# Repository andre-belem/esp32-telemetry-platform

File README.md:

# Real-Time ESP32 Web Monitoring

Real-time IoT telemetry and remote monitoring platform using ESP32, MQTT, Node.js, Docker, and MySQL.

## Overview

This project was developed to demonstrate a complete IoT monitoring architecture capable of collecting, transmitting, storing, and visualizing real-time sensor data from an ESP32 device to a dedicated web server.

The system is designed with scalability and modularity in mind, combining embedded systems, backend development, networking, and data visualization technologies.

## Features

- Real-time sensor monitoring
- ESP32 Wi-Fi communication
- MQTT-based telemetry
- REST API integration
- Data storage using MySQL
- Web dashboard for live visualization
- Remote access through a dedicated Linux server
- Dockerized backend services
- Scalable IoT architecture

## System Architecture

````
+------------------+
|      ESP32       |
| Sensors & Data   |
+--------+---------+
         |
         | Wi-Fi / MQTT
         |
+--------v---------+
|   MQTT Broker    |
+--------+---------+
         |
         |
+--------v---------+
|  Node.js Backend |
|   REST API       |
+--------+---------+
         |
         |
+--------v---------+
|      MySQL       |
|   Data Storage   |
+--------+---------+
         |
         |
+--------v---------+
| Web Dashboard    |
| Real-Time Charts |
+------------------+

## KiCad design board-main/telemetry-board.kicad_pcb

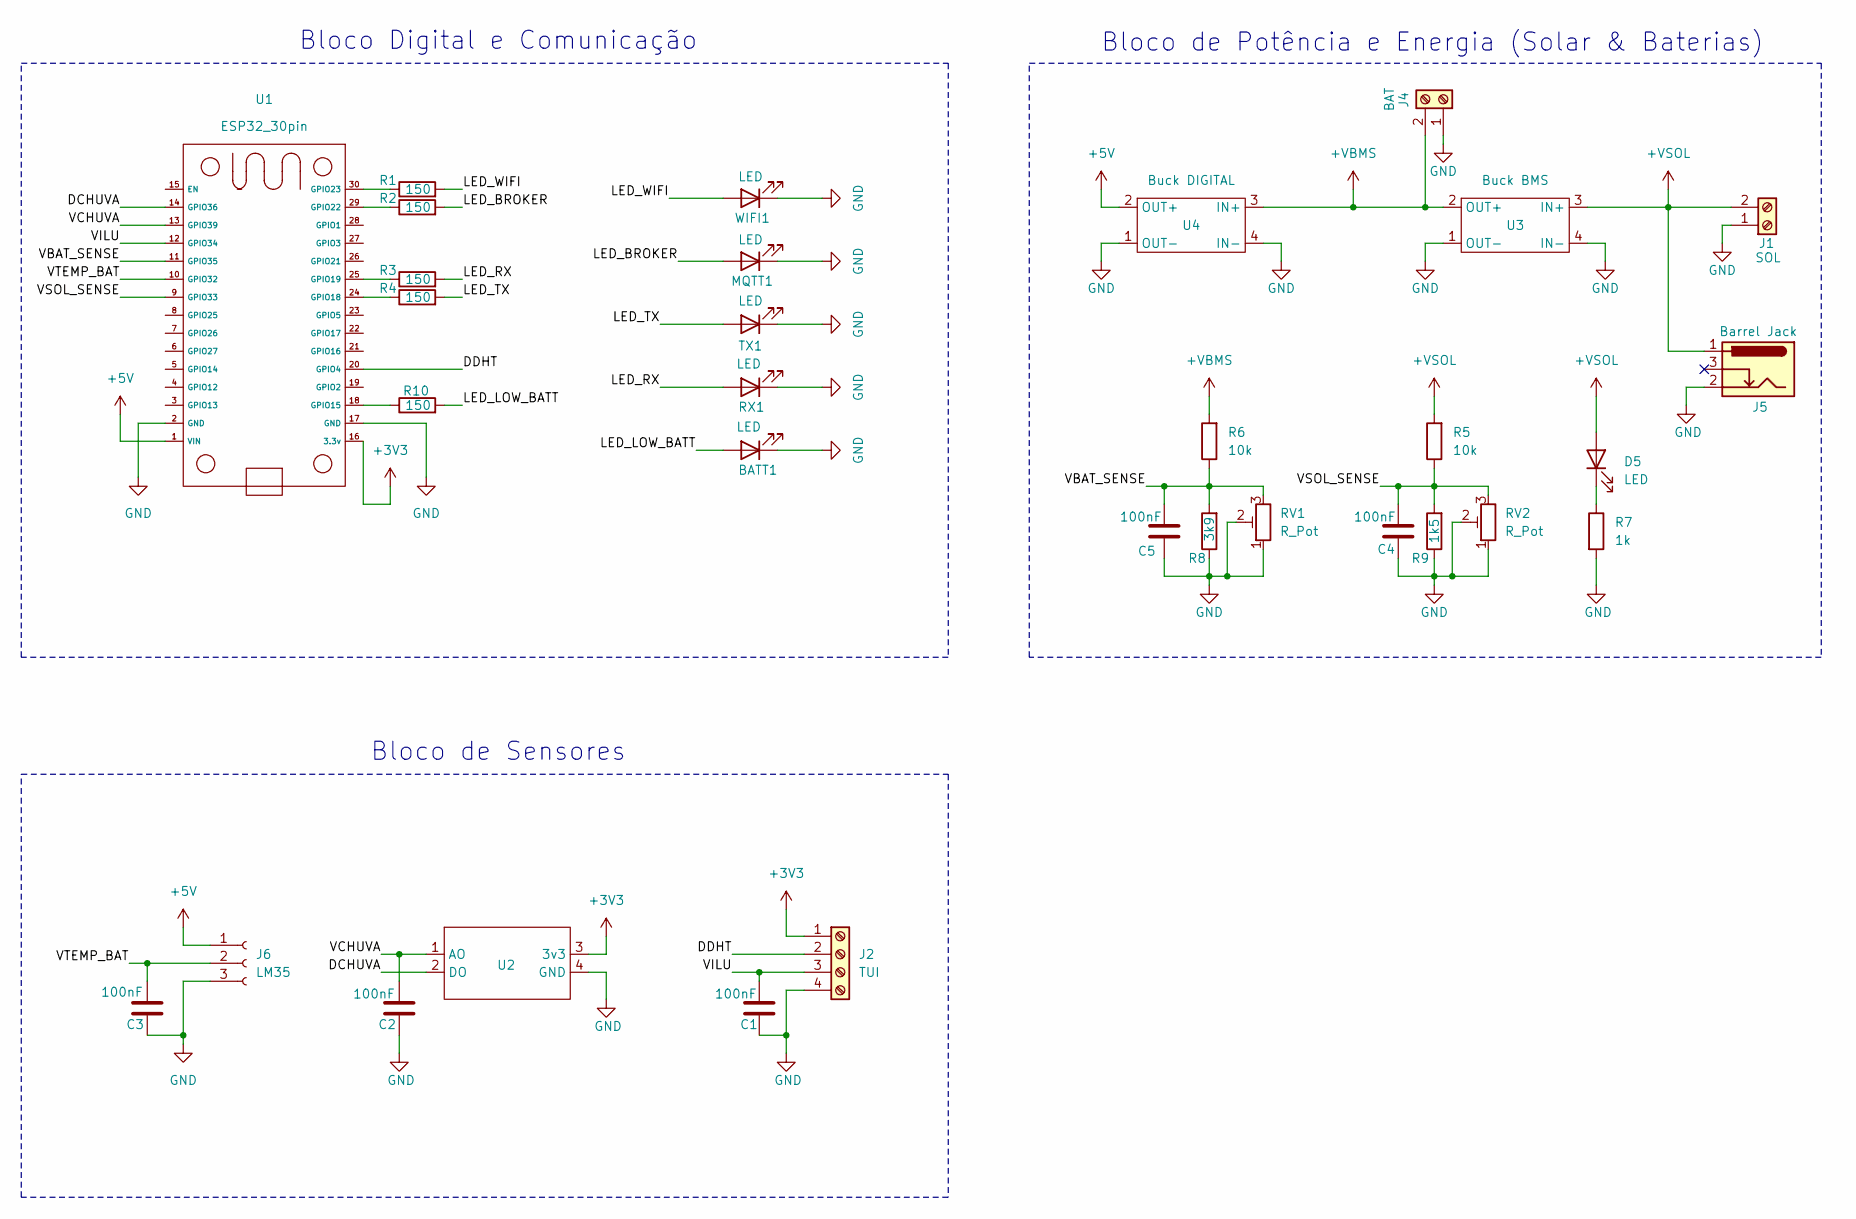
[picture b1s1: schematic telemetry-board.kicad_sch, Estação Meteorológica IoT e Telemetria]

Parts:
BATT1: LED; LED_D5.0mm
C1, C2, C3, C4, C5: 100nF; C_Disc_D5.0mm_W2.5mm_P2.50mm
D5: LED; LED_D5.0mm
J1: SOL; TerminalBlock_Phoenix_PT-1,5-2-5.0-H_1x02_P5.00mm_Horizontal
J2: TUI; TerminalBlock_Phoenix_PT-1,5-4-5.0-H_1x04_P5.00mm_Horizontal
J4: BAT; TerminalBlock_Phoenix_PT-1,5-2-5.0-H_1x02_P5.00mm_Horizontal
J5: Barrel Jack; BarrelJack_CUI_PJ-102AH_Horizontal
J6: LM35; PinSocket_1x03_P2.54mm_Vertical
MQTT1: LED; LED_D5.0mm
R1, R2, R3, R4, R10: 150; R_Axial_DIN0207_L6.3mm_D2.5mm_P7.62mm_Horizontal
R5, R6: 10k; R_Axial_DIN0207_L6.3mm_D2.5mm_P7.62mm_Horizontal
R7: 1k; R_Axial_DIN0207_L6.3mm_D2.5mm_P7.62mm_Horizontal
R8: 3k9; R_Axial_DIN0207_L6.3mm_D2.5mm_P7.62mm_Horizontal
R9: 1k5; R_Axial_DIN0207_L6.3mm_D2.5mm_P7.62mm_Horizontal
RV1, RV2: R_Pot; Potentiometer_Bourns_3296W_Vertical
RX1: LED; LED_D5.0mm
TX1: LED; LED_D5.0mm
U1: ESP32_30pin
U2: Rain Module
U3: Buck BMS; Modulo_LM2596_Direto
U4: Buck DIGITAL; Modulo_LM2596_Direto
WIFI1: LED; LED_D5.0mm

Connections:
+3V3: J2.1, U1.16 (3.3v), U2.3 (3v3)
+5V: J6.1, U1.1 (VIN), U4.2 (OUT+)
+VBMS: J4.2, R6.2, U3.2 (OUT+), U4.3 (IN+)
+VSOL: D5.2 (A), J1.2, J5.1, R5.2, U3.3 (IN+)
/DCHUVA: U1.14 (GPIO36), U2.2 (DO)
/DDHT: J2.2, U1.20 (GPIO4)
/LED_BROKER: MQTT1.2 (A), R2.2
/LED_LOW_BATT: BATT1.2 (A), R10.2
/LED_RX: R3.2, RX1.2 (A)
/LED_TX: R4.2, TX1.2 (A)
/LED_WIFI: R1.2, WIFI1.2 (A)
/VBAT_SENSE: C5.1, R6.1, R8.2, RV1.3, U1.11 (GPIO35)
/VCHUVA: C2.1, U1.13 (GPIO39), U2.1 (AO)
/VILU: C1.1, J2.3, U1.12 (GPIO34)
/VSOL_SENSE: C4.1, R5.1, R9.2, RV2.3, U1.9 (GPIO33)
/VTEMP_BAT: C3.1, J6.2, U1.10 (GPIO32)
GND: BATT1.1 (K), C1.2, C2.2, C3.2, C4.2, C5.2, J1.1, J2.4, J4.1, J5.2, J6.3, MQTT1.1 (K), R7.2, R8.1, R9.1, RV1.1, RV1.2, RV2.1, RV2.2, RX1.1 (K), TX1.1 (K), U1.2 (GND), U1.17 (GND), U2.4 (GND), U3.1 (OUT-), U3.4 (IN-), U4.1 (OUT-), U4.4 (IN-), WIFI1.1 (K)
unnamed: D5.1 (K), R7.1
unnamed: R10.1, U1.18 (GPIO15)
unnamed: R4.1, U1.24 (GPIO18)
unnamed: R3.1, U1.25 (GPIO19)
unnamed: R2.1, U1.29 (GPIO22)
unnamed: R1.1, U1.30 (GPIO23)

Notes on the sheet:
Bloco de Potência e Energia (Solar & Baterias)
Bloco Digital e Comunicação
Bloco de Sensores

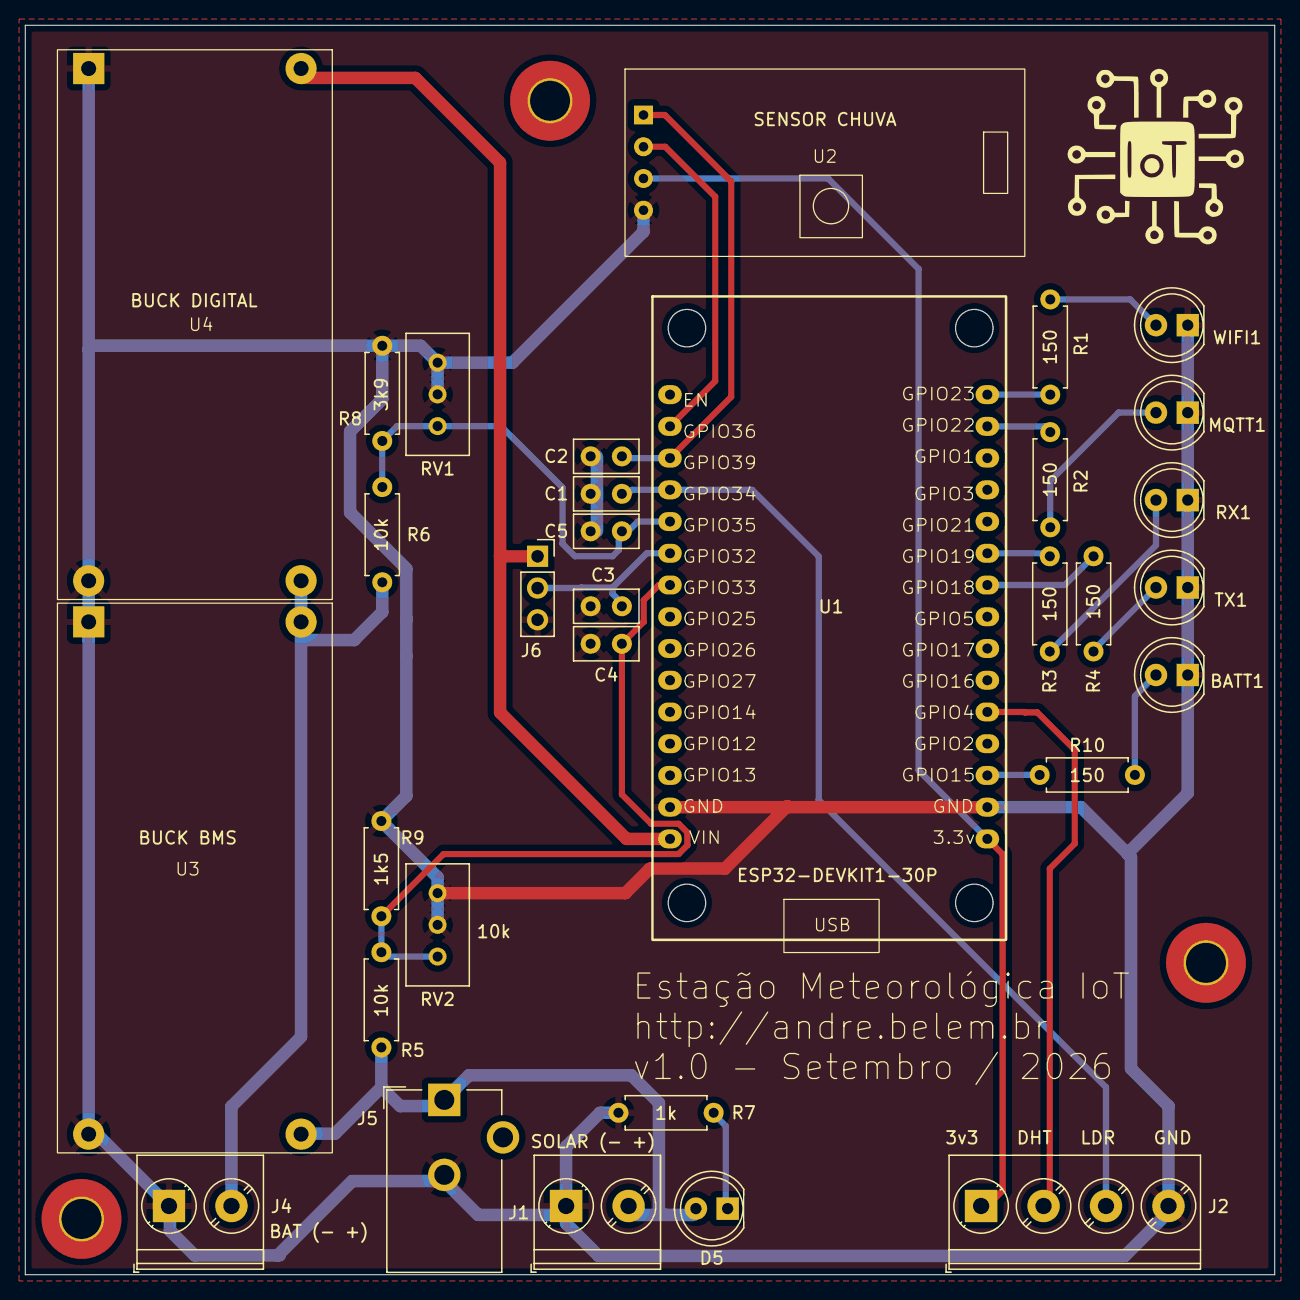
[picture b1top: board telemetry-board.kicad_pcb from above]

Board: 2 copper layers, 100.0 x 100.0 mm, 32 parts (0 on the bottom side), 23 nets.

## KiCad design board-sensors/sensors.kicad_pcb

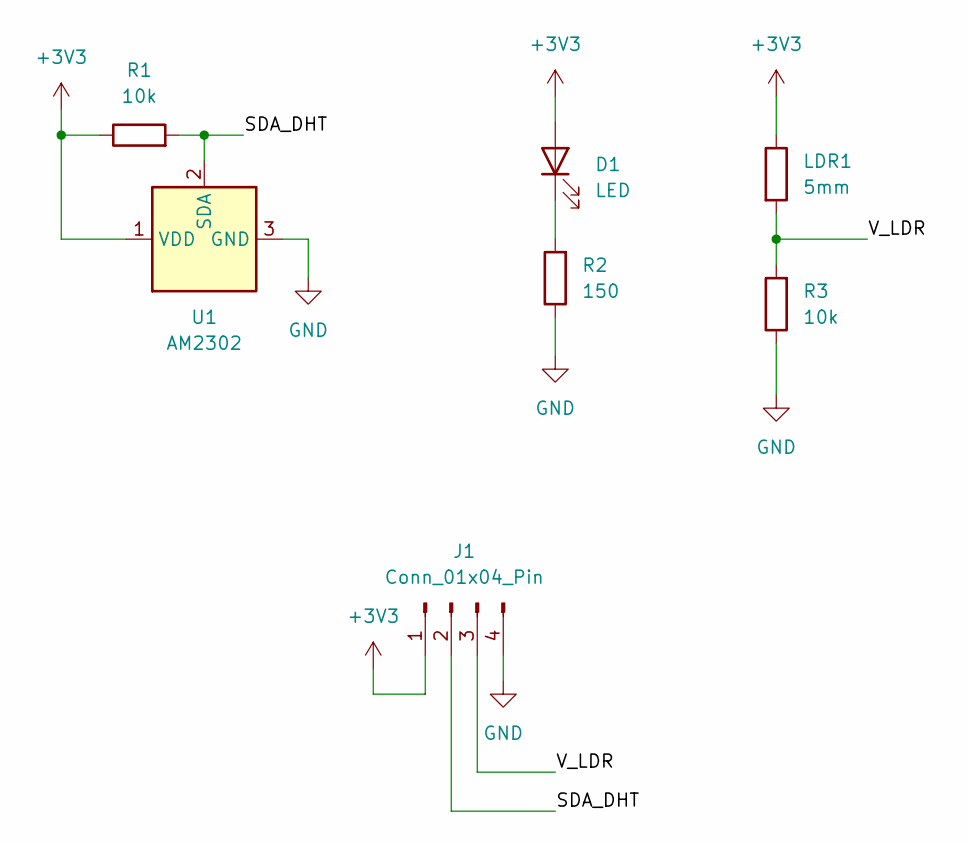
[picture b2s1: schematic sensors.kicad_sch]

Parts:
D1: LED; LED_D3.0mm
J1: Conn_01x04_Pin; PinHeader_1x04_P2.54mm_Vertical
LDR1: 5mm; R_LDR_5.0x4.1mm_P3mm_Vertical
R1, R3: 10k; R_Axial_DIN0207_L6.3mm_D2.5mm_P7.62mm_Horizontal
R2: 150; R_Axial_DIN0207_L6.3mm_D2.5mm_P7.62mm_Horizontal
U1: AM2302; ASAIR_AM2302_P2.54mm_Lead2.75mm_TabDown

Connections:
+3V3: D1.2 (A), J1.1, LDR1.1, R1.1, U1.1 (VDD)
/SDA_DHT: J1.2, R1.2, U1.2 (SDA)
/V_LDR: J1.3, LDR1.2, R3.2
GND: J1.4, R2.1, R3.1, U1.3 (GND), U1.4 (GND)
unnamed: D1.1 (K), R2.2

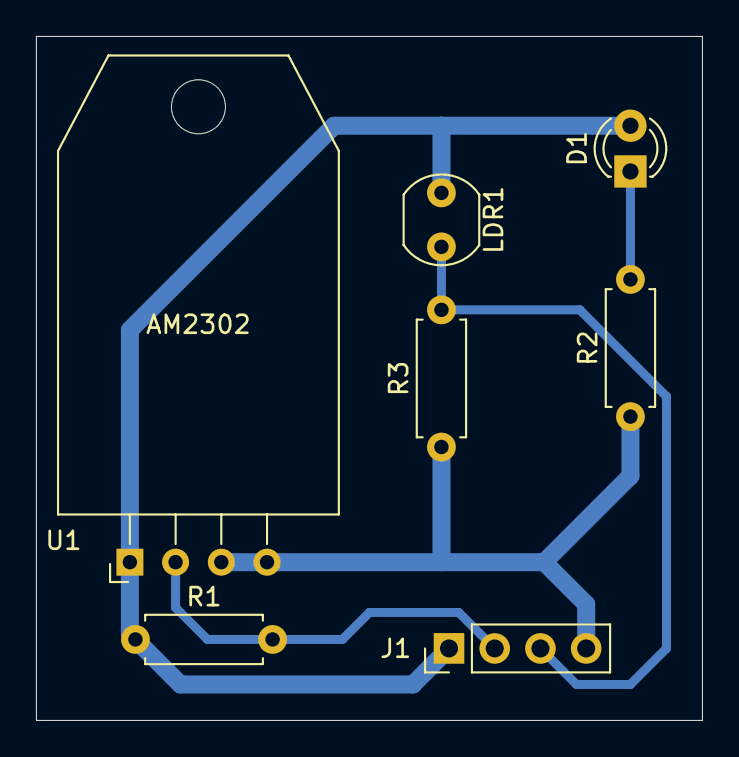
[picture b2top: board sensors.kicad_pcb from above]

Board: 2 copper layers, 37.0 x 38.0 mm, 7 parts (0 on the bottom side), 5 nets.
